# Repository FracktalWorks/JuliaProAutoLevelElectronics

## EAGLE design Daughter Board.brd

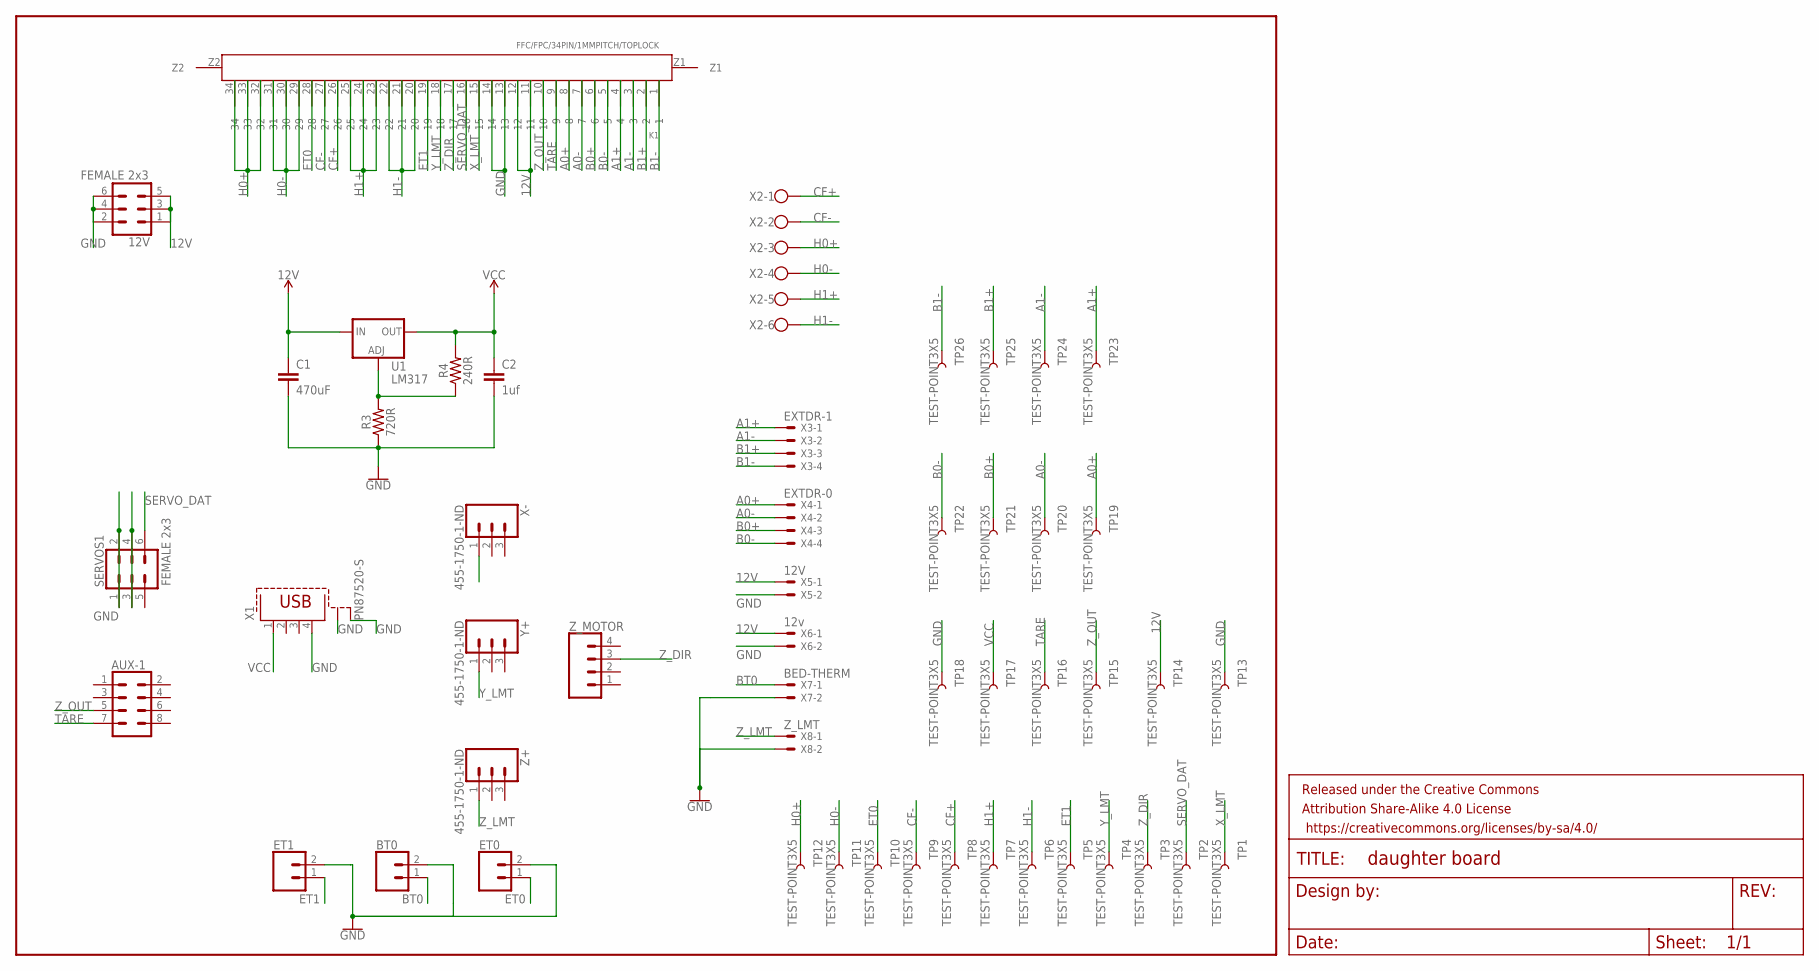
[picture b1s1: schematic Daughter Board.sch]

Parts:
12V: FEMALE 2x3; 2X3
AUX-1: CONN_04X2; 2X4
BT0: CONN_02; 1X02
C1: 470uF; 0603
C2: 1uf; 0603
ET0, ET1: CONN_02; 1X02
FRAME1: FRAME-LETTERNO_PACKAGE; DUMMY
K1: FFC/FPC/34PIN/1MMPITCH/TOPLOCK; 34PIN/1MMPITCH/FFC/FPC
R3: 720R; 0603
R4: 240R; 0603
SERVOS1: FEMALE 2x3; 2X3
TP1, TP2, TP3, TP4, TP5, TP6, TP7, TP8, TP9, TP10, TP11, TP12, TP13, TP14, TP15, TP16, TP17, TP18, TP19, TP20, TP21, TP22, TP23, TP24, TP25, TP26: TEST-POINT3X5; PAD.03X.05
U1: LM317; TO220-ADJ
X1: PN87520-S
X2: W237-6
X3: EXTDR-1; JST-XH-04-PACKAGE-LONG-PAD
X4: EXTDR-0; JST-XH-04-PACKAGE-LONG-PAD
X5: 12V; JST-XH-02-PACKAGE-LONG-PAD
X6: 12v; JST-XH-02-PACKAGE-LONG-PAD
X7: BED-THERM; JST-XH-02-PACKAGE-LONG-PAD
X8: Z_LMT; JST-XH-02-PACKAGE-LONG-PAD
X-: 455-1750-1-ND; 1X03
Y+: 455-1750-1-ND; 1X03
Z+: 455-1750-1-ND; 1X03
Z_MOTOR: CONN_04; 1X04

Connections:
12V: 12V.1, 12V.3, 12V.5, C1.1, K1.11, K1.12, TP14.P$1, U1.IN, X5.1, X6.1
A0+: K1.8, TP19.P$1, X4.1
A0-: K1.7, TP20.P$1, X4.2
A1+: K1.4, TP23.P$1, X3.1
A1-: K1.3, TP24.P$1, X3.2
ADJ: R3.2, R4.1, U1.ADJ
B0+: K1.6, TP21.P$1, X4.3
B0-: K1.5, TP22.P$1, X4.4
B1+: K1.2, TP25.P$1, X3.3
B1-: K1.1, TP26.P$1, X3.4
BT0: BT0.1, X7.1
CF+: K1.26, TP8.P$1, X2.1
CF-: K1.27, TP9.P$1, X2.2
ET0: ET0.1, K1.28, TP10.P$1
ET1: ET1.1, K1.19, TP5.P$1
GND: 12V.2, 12V.4, 12V.6, BT0.2, C1.2, C2.2, ET0.2, ET1.2, K1.13, K1.14, R3.1, SERVOS1.1, SERVOS1.2, TP13.P$1, TP18.P$1, X1.4, X1.S1, X1.S2, X5.2, X6.2, X7.2, X8.2
H0+: K1.32, K1.33, K1.34, TP12.P$1, X2.3
H0-: K1.29, K1.30, K1.31, TP11.P$1, X2.4
H1+: K1.23, K1.24, K1.25, TP7.P$1, X2.5
H1-: K1.20, K1.21, K1.22, TP6.P$1, X2.6
unnamed: SERVOS1.3, SERVOS1.4
SERVO_DAT: K1.16, SERVOS1.6, TP2.P$1
TARE: AUX-1.7, K1.9, TP16.P$1
VCC: C2.1, R4.2, TP17.P$1, U1.OUT, X1.1
X_LMT: K1.15, TP1.P$1, X-.1
Y_LMT: K1.18, TP4.P$1, Y+.1
Z_DIR: K1.17, TP3.P$1, Z_MOTOR.3
Z_LMT: X8.1, Z+.1
Z_OUT: AUX-1.5, K1.10, TP15.P$1

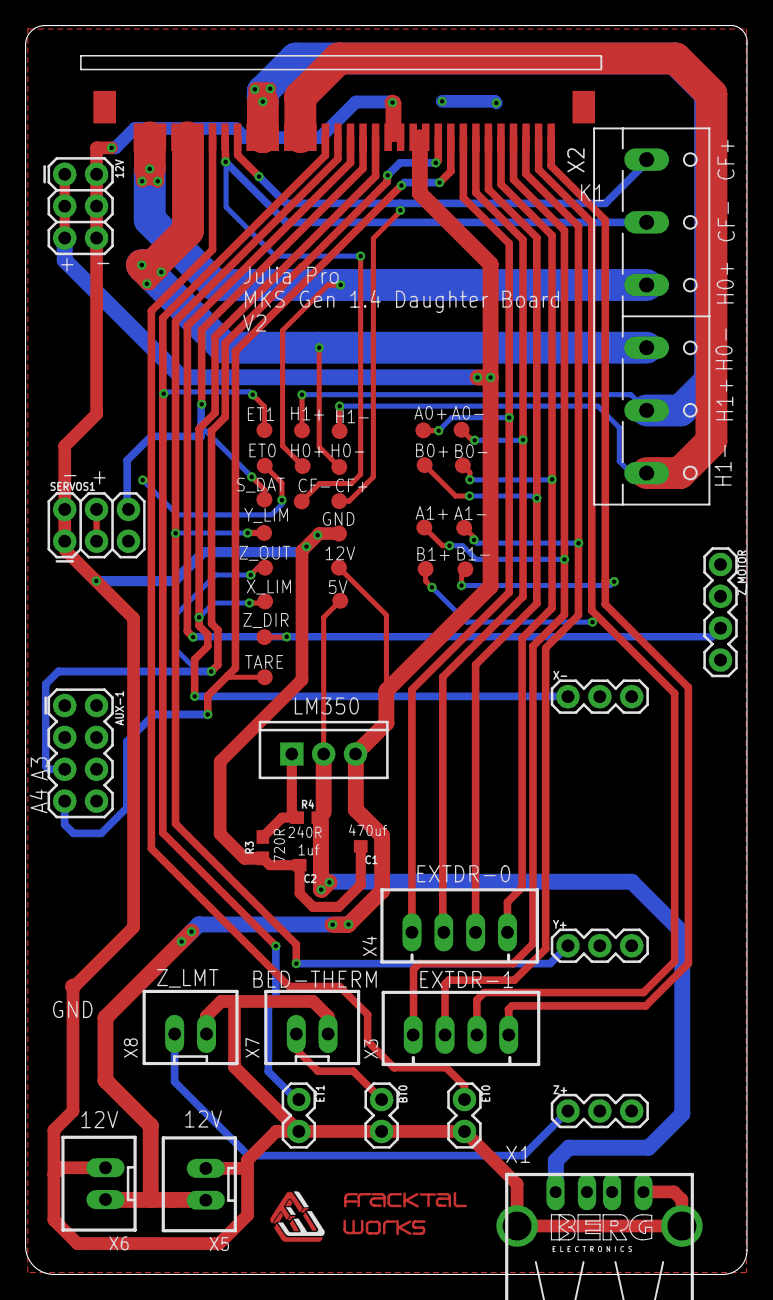
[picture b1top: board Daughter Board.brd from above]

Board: 2 copper layers, 57.5 x 99.6 mm, 52 parts (0 on the bottom side), 29 nets.

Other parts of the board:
U$1: FWLOGO_SMALL_FOOTPRINT; FWLOGO_SMALL

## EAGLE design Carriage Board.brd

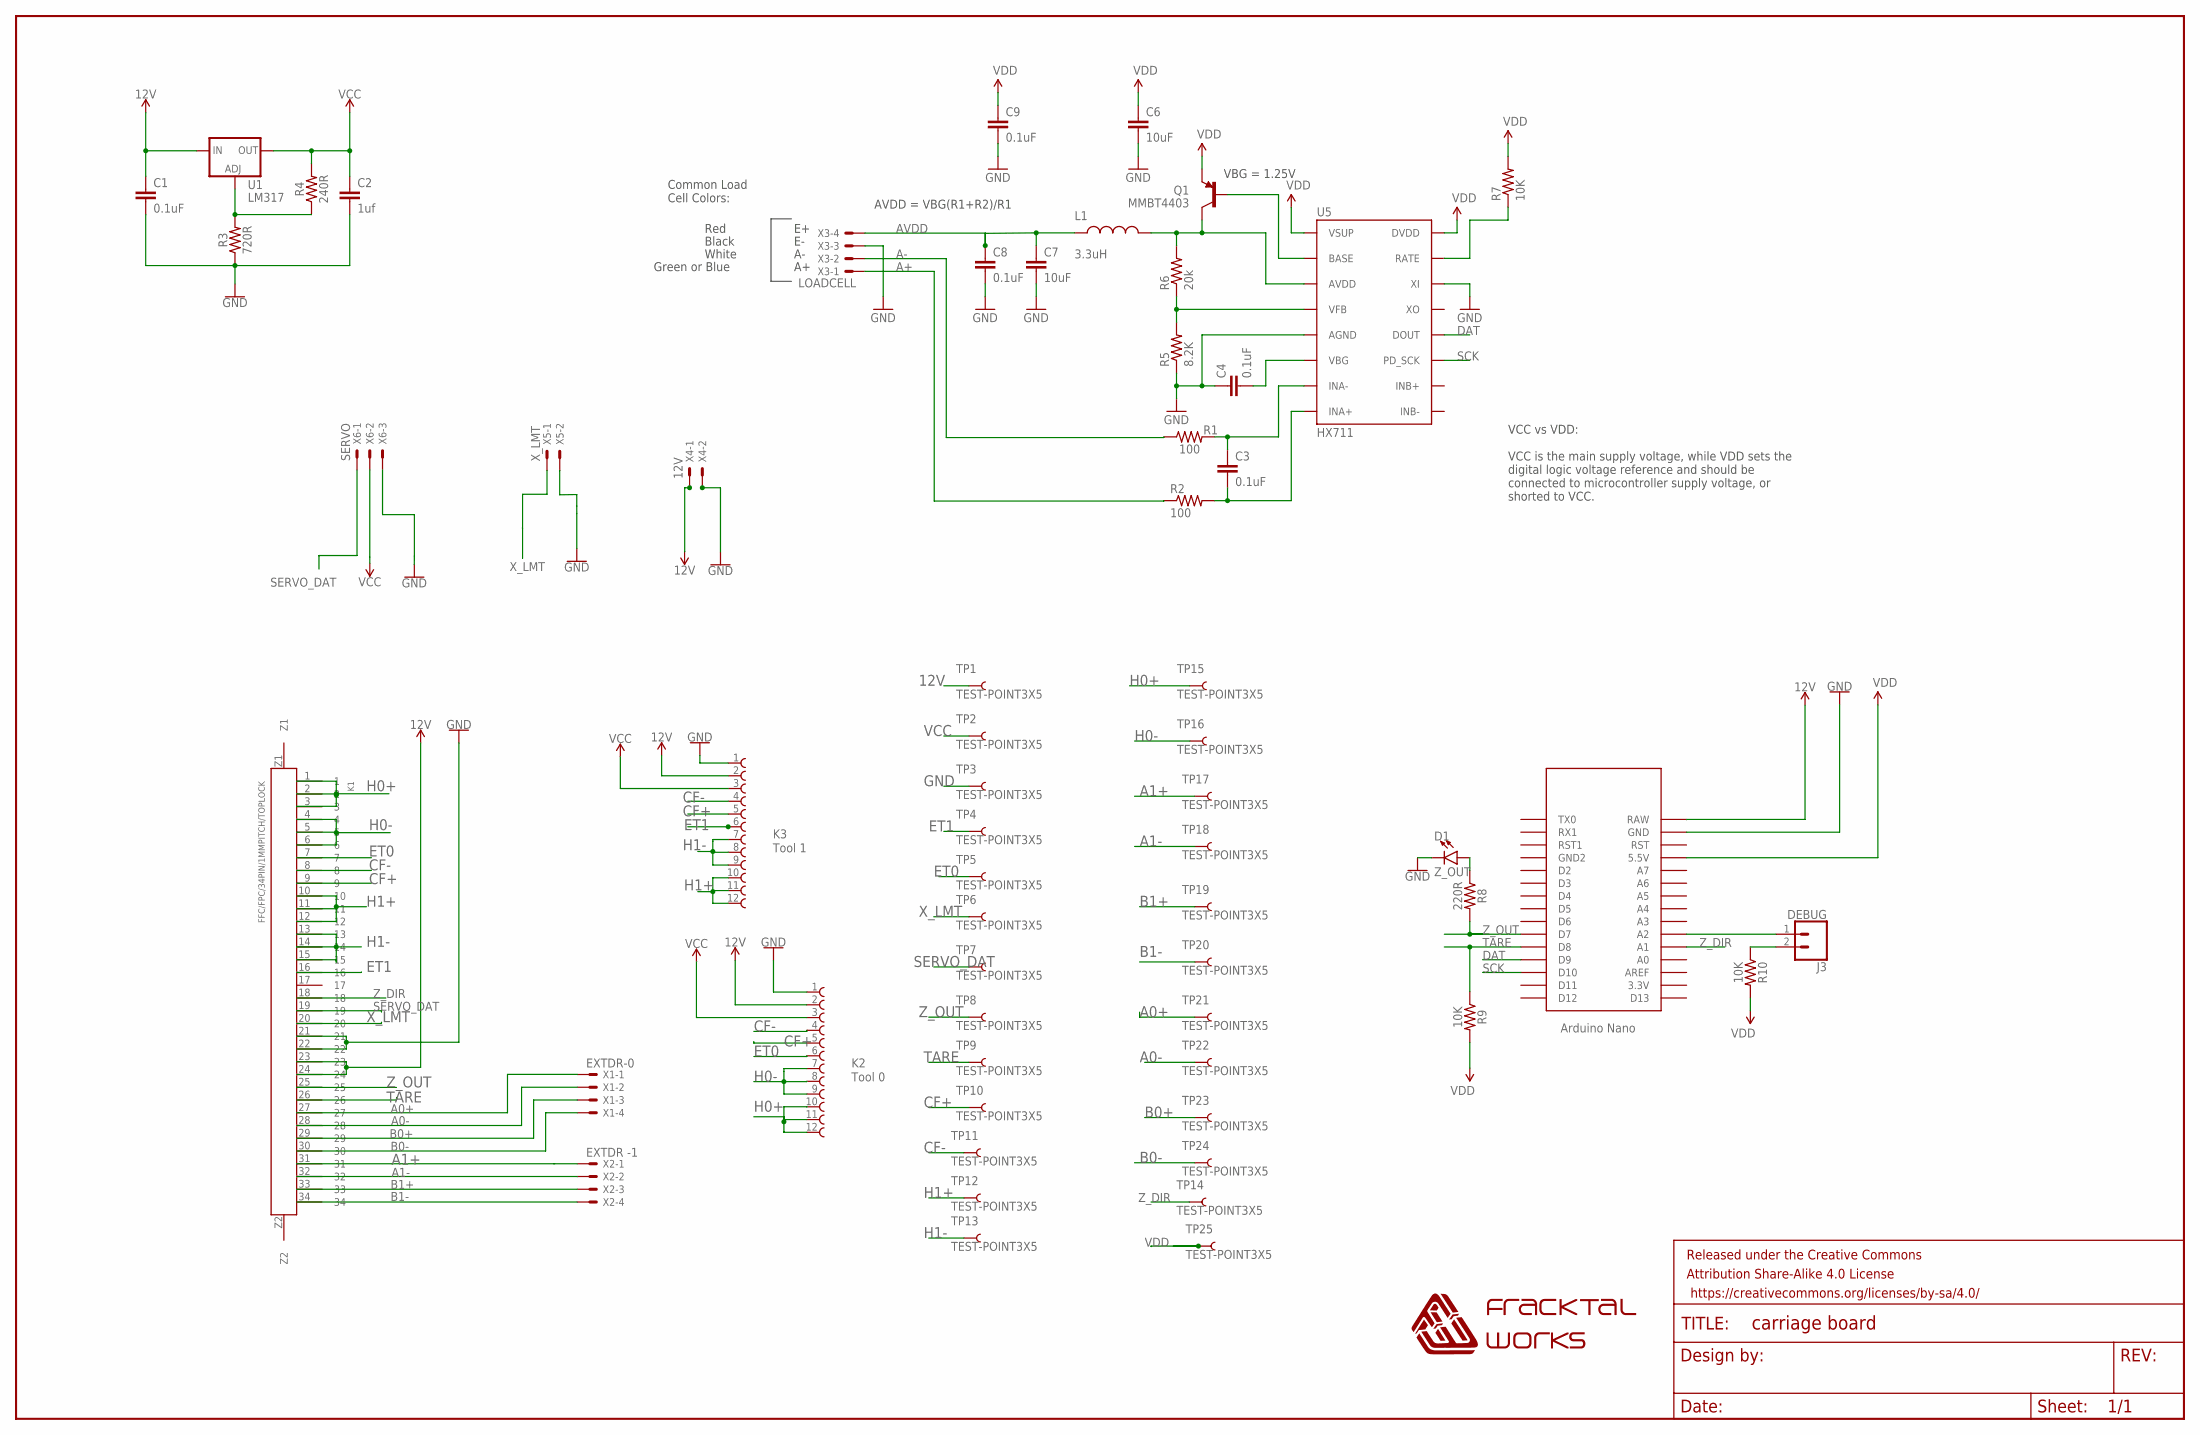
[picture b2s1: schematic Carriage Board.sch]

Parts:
C1: 0.1uF; 0603
C2: 1uf; 0603
C3, C4, C8, C9: 0.1uF; 0603-CAP
C6, C7: 10uF; 1210
D1: Z_OUT; LED_3MM
FRAME1: FRAME-LEDGER; CREATIVE_COMMONS
J3: DEBUG; 1X02
K1: FFC/FPC/34PIN/1MMPITCH/TOPLOCK; 34PIN/1MMPITCH/FFC/FPC
K2: Tool 0; 68611214122
K3: Tool 1; 68611214122
L1: 3.3uH; 0805
Q1: MMBT4403; SOT23-3
R1, R2: 100; 0603-RES
R3: 720R; 0603
R4: 240R; 0603
R5: 8.2K; 0603-RES
R6: 20k; 0603-RES
R7: 10K; 0603-RES
R8: 220R; 0603
R9, R10: 10K; 0603
TP1, TP2, TP3, TP4, TP5, TP6, TP7, TP8, TP9, TP10, TP11, TP12, TP13, TP14, TP15, TP16, TP17, TP18, TP19, TP20, TP21, TP22, TP23, TP24, TP25: TEST-POINT3X5; PAD.03X.05
U1: LM317; SOT223
U5: HX711; SO16
U$1: NANO
U$2: FWLOGO
X1: EXTDR-0; JST-XH-04-PACKAGE-LONG-PAD
X2: EXTDR -1; JST-XH-04-PACKAGE-LONG-PAD
X3: LOADCELL; JST-XH-04-PACKAGE-LONG-PAD
X4: 12V; JST-XH-02-PACKAGE-LONG-PAD
X5: X_LMT; JST-XH-02-PACKAGE-LONG-PAD
X6: SERVO; JST-XH-03-PACKAGE-LONG-PAD

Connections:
12V: C1.1, K1.23, K1.24, K2.2, K3.2, TP1.P$1, U1.3 (IN), U$1.RAW, X4.1
A0+: K1.27, TP21.P$1, X1.1
A0-: K1.28, TP22.P$1, X1.2
A1+: K1.31, TP17.P$1, X2.1
A1-: K1.32, TP18.P$1, X2.2
A+: R2.1, X3.1
A-: R1.1, X3.2
ADJ: R3.2, R4.1, U1.1 (ADJ)
AVDD: C7.1, C8.1, L1.1, X3.4
B0+: K1.29, TP23.P$1, X1.3
B0-: K1.30, TP24.P$1, X1.4
B1+: K1.33, TP19.P$1, X2.3
B1-: K1.34, TP20.P$1, X2.4
CF+: K1.9, K2.5, K3.5, TP10.P$1
CF-: K1.8, K2.4, K3.4, TP11.P$1
DAT: U5.12 (DOUT), U$1.D9
ET0: K1.7, K2.6, TP5.P$1
ET1: K1.16, K3.6, TP4.P$1
GND: C1.2, C2.2, C4.1, C6.2, C7.2, C8.2, C9.2, D1.K (C), K1.21, K1.22, K2.1, K3.1, R3.1, R5.1, TP3.P$1, U5.5 (AGND), U5.14 (XI), U$1.GND, X3.3, X4.2, X5.2, X6.3
H0+: K1.1, K1.2, K1.3, K2.10, K2.11, K2.12, TP15.P$1
H0-: K1.4, K1.5, K1.6, K2.7, K2.8, K2.9, TP16.P$1
H1+: K1.10, K1.11, K1.12, K3.10, K3.11, K3.12, TP12.P$1
H1-: K1.13, K1.14, K1.15, K3.7, K3.8, K3.9, TP13.P$1
unnamed: R7.1, U5.15 (RATE)
unnamed: C3.1, R1.2, U5.7 (INA-)
unnamed: Q1.1 (B), U5.2 (BASE)
unnamed: L1.2, Q1.3 (C), R6.2, U5.3 (AVDD)
unnamed: R5.2, R6.1, U5.4 (VFB)
unnamed: C4.2, U5.6 (VBG)
unnamed: C3.2, R2.2, U5.8 (INA+)
unnamed: J3.1, U$1.A2
unnamed: J3.2, R10.1
unnamed: D1.A, R8.1
SCK: U5.11 (PD_SCK), U$1.D10
SERVO_DAT: K1.19, TP7.P$1, X6.1
TARE: K1.26, R9.1, TP9.P$1, U$1.D8
VCC: C2.1, K2.3, K3.3, R4.2, TP2.P$1, U1.2 (OUT), X6.2
VDD: C6.1, C9.1, Q1.2 (E), R7.2, R9.2, R10.2, TP25.P$1, U5.1 (VSUP), U5.16 (DVDD), U$1.5V (5.5V)
X_LMT: K1.20, TP6.P$1, X5.1
Z_DIR: K1.18, TP14.P$1, U$1.A1
Z_OUT: K1.25, R8.2, TP8.P$1, U$1.D7

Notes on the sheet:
VBG = 1.25V
AVDD = VBG(R1+R2)/R1
Red
Black
White
Green or Blue
Common Load Cell Colors:
VCC vs VDD: VCC is the main supply voltage, while VDD sets the digital logic voltage reference and should be connected to microcontroller supply voltage, or shorted to VCC.

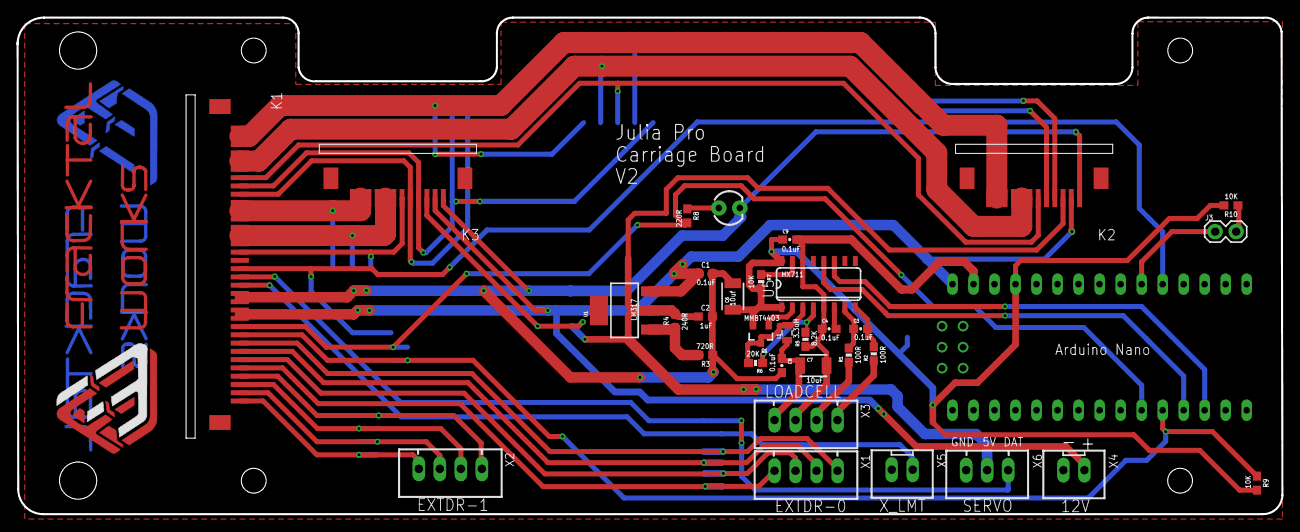
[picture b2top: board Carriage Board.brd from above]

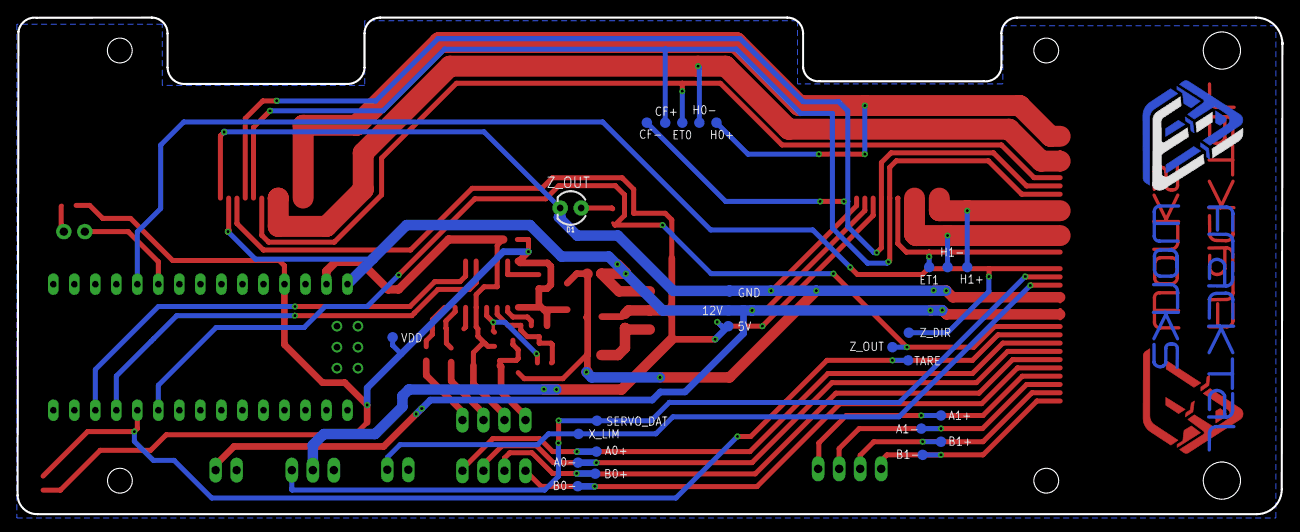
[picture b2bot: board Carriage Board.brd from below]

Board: 2 copper layers, 152.9 x 60.0 mm, 62 parts (27 on the bottom side), 41 nets.

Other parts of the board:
U$3: FWLOGO_FOOTPRINT; FWLOGO

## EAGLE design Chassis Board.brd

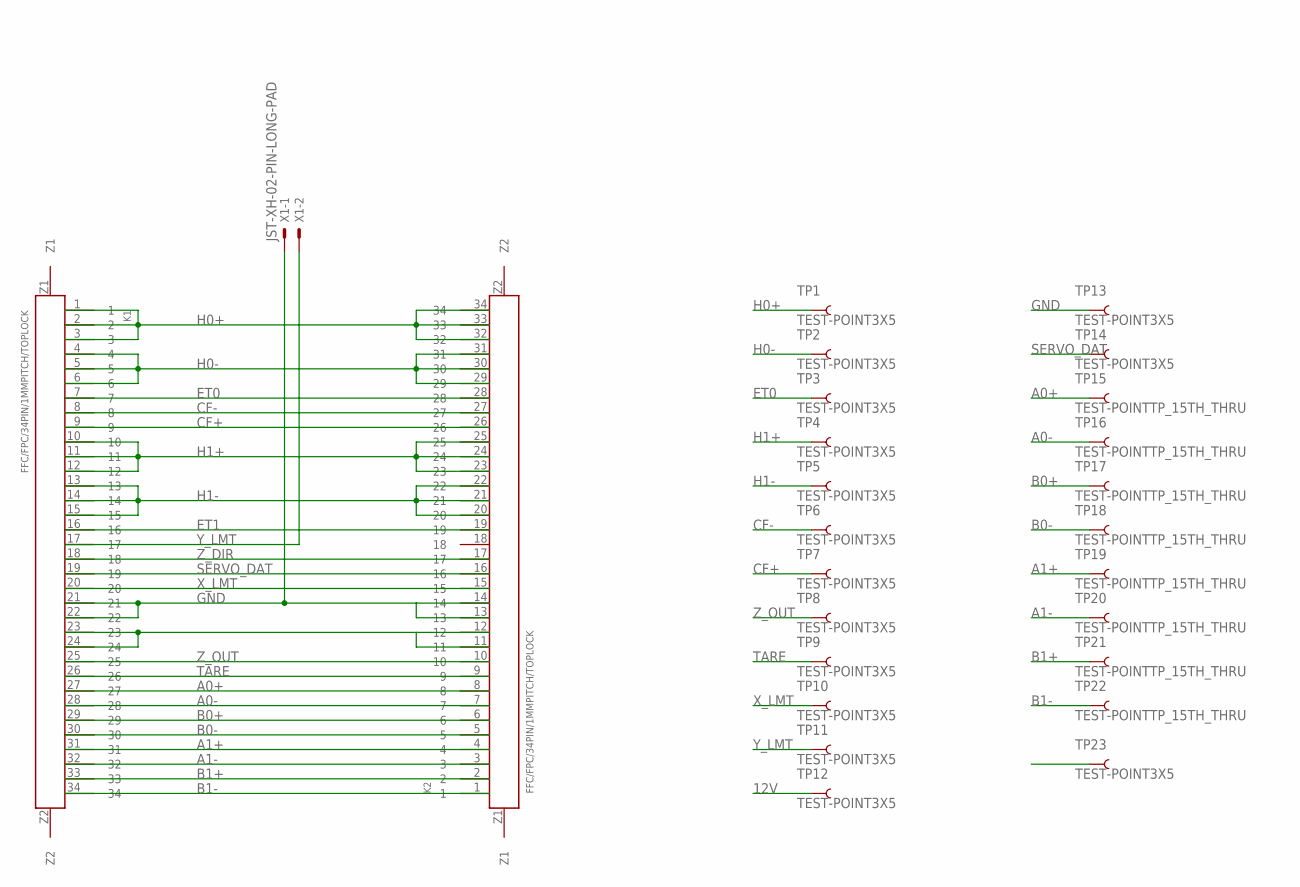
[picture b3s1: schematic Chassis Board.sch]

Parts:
K1, K2: FFC/FPC/34PIN/1MMPITCH/TOPLOCK; 34PIN/1MMPITCH/FFC/FPC
TP1, TP2, TP3, TP4, TP5, TP6, TP7, TP8, TP9, TP10, TP11, TP12, TP13, TP14, TP23: TEST-POINT3X5; PAD.03X.05
TP15, TP16, TP17, TP18, TP19, TP20, TP21, TP22: TEST-POINTTP_15TH_THRU; TP_15TH
X1: JST-XH-02-PIN-LONG-PAD; JST-XH-02-PACKAGE-LONG-PAD

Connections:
12V: K1.23, K1.24, K2.11, K2.12, TP12.P$1
A0+: K1.27, K2.8, TP15.P$1
A0-: K1.28, K2.7, TP16.P$1
A1+: K1.31, K2.4, TP19.P$1
A1-: K1.32, K2.3, TP20.P$1
B0+: K1.29, K2.6, TP17.P$1
B0-: K1.30, K2.5, TP18.P$1
B1+: K1.33, K2.2, TP21.P$1
B1-: K1.34, K2.1, TP22.P$1
CF+: K1.9, K2.26, TP7.P$1
CF-: K1.8, K2.27, TP6.P$1
ET0: K1.7, K2.28, TP3.P$1
ET1: K1.16, K2.19, TP23.P$1
GND: K1.21, K1.22, K2.13, K2.14, TP13.P$1, X1.1
H0+: K1.1, K1.2, K1.3, K2.32, K2.33, K2.34, TP1.P$1
H0-: K1.4, K1.5, K1.6, K2.29, K2.30, K2.31, TP2.P$1
H1+: K1.10, K1.11, K1.12, K2.23, K2.24, K2.25, TP4.P$1
H1-: K1.13, K1.14, K1.15, K2.20, K2.21, K2.22, TP5.P$1
SERVO_DAT: K1.19, K2.16, TP14.P$1
TARE: K1.26, K2.9, TP9.P$1
X_LMT: K1.20, K2.15, TP10.P$1
Y_LMT: K1.17, TP11.P$1, X1.2
Z_DIR: K1.18, K2.17
Z_OUT: K1.25, K2.10, TP8.P$1

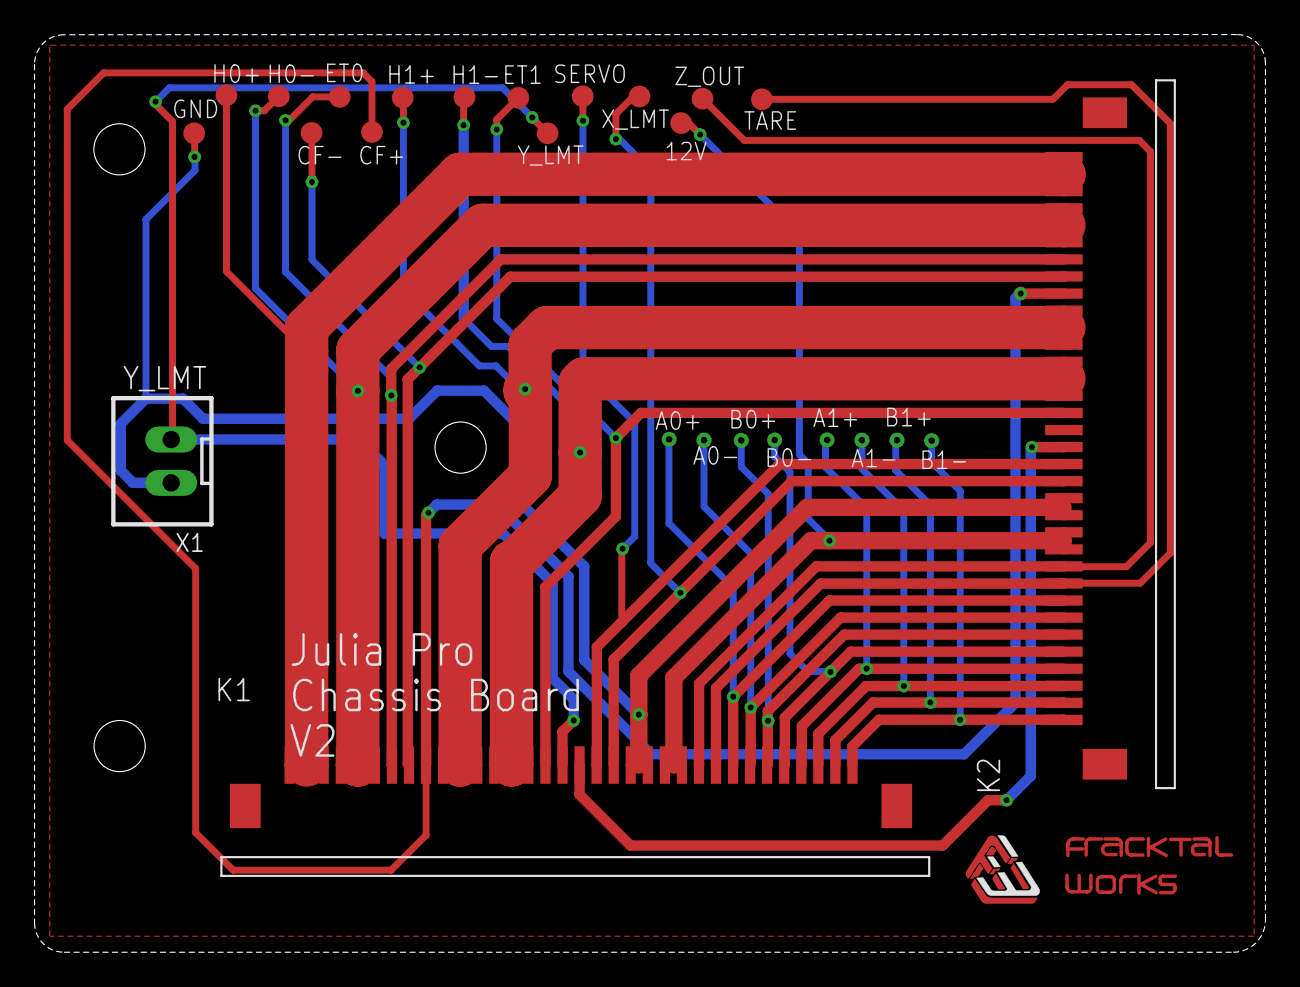
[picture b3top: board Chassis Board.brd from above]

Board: 2 copper layers, 72.2 x 53.8 mm, 27 parts (0 on the bottom side), 24 nets.

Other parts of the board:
U$1: FWLOGO_SMALL_FOOTPRINT; FWLOGO_SMALL

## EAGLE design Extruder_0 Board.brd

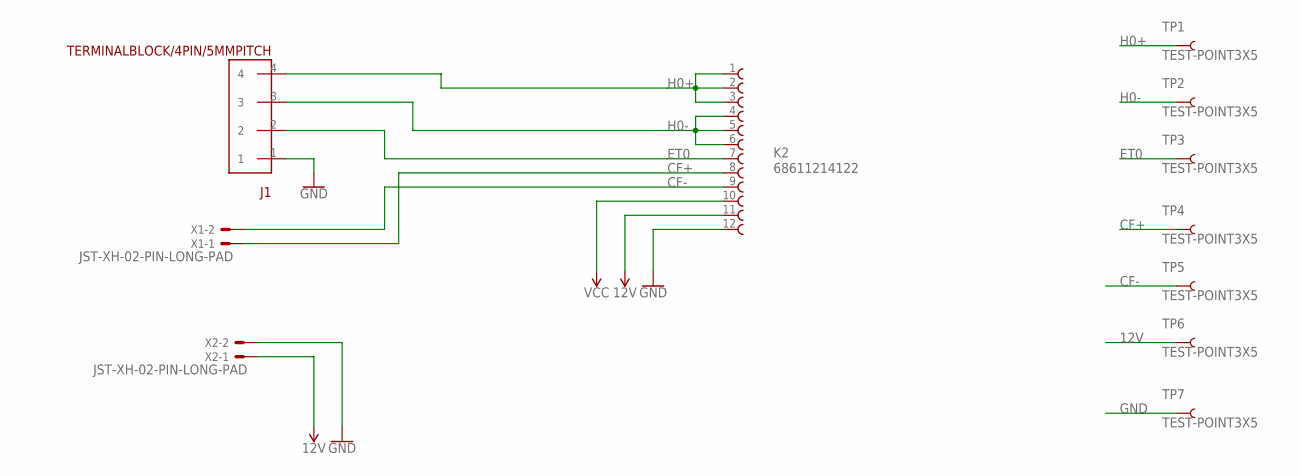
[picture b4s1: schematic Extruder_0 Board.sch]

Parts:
J1: TERMINALBLOCK/4PIN/5MMPITCH; TERMINALBLOCK/TOYO/4PIN/5MMPITCH
K2: 68611214122
TP1, TP2, TP3, TP4, TP5, TP6, TP7: TEST-POINT3X5; PAD.03X.05
X1, X2: JST-XH-02-PIN-LONG-PAD; JST-XH-02-PACKAGE-LONG-PAD

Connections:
12V: K2.11, TP6.P$1, X2.1
CF+: K2.8, TP4.P$1, X1.1
CF-: K2.9, TP5.P$1, X1.2
ET0: J1.2, K2.7, TP3.P$1
GND: J1.1, K2.12, TP7.P$1, X2.2
H0+: J1.4, K2.1, K2.2, K2.3, TP1.P$1
H0-: J1.3, K2.4, K2.5, K2.6, TP2.P$1
VCC: K2.10

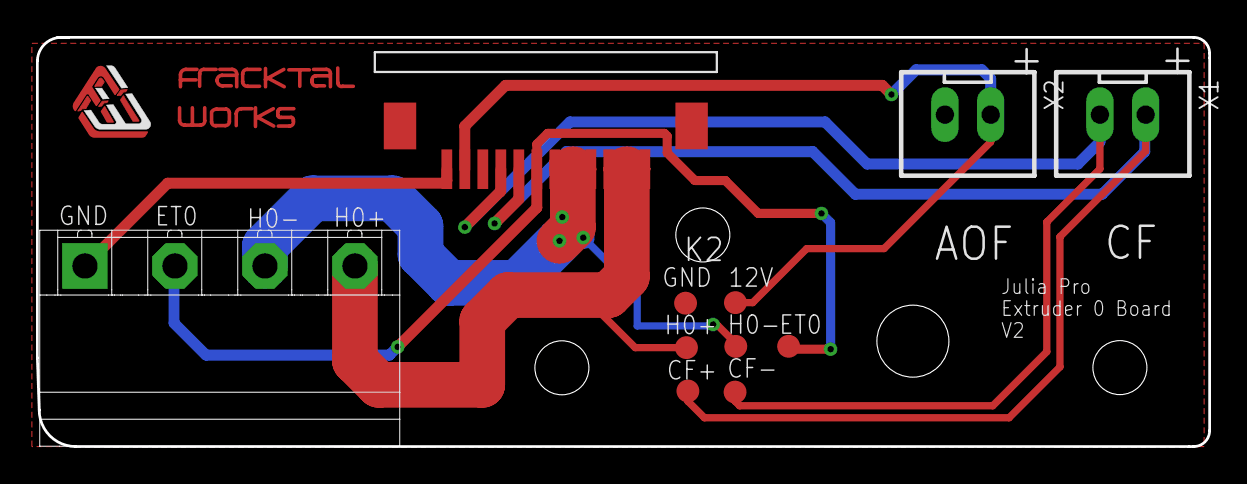
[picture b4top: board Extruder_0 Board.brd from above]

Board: 2 copper layers, 65.1 x 22.7 mm, 12 parts (0 on the bottom side), 7 nets.

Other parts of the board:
U$1: FWLOGO_SMALL_FOOTPRINT; FWLOGO_SMALL

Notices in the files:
parts and their libraries:
SparkFun-Capacitors: Licensing: Creative Commons ShareAlike 4.0 International - https://creativecommons.org/licenses/by-sa/4.0
SparkFun-Connectors: Licensing: CC v3.0 Share-Alike You are welcome to use this library for commercial purposes.
SparkFun-Aesthetics: Released under the Creative Commons
